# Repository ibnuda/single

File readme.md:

# Single PCB

## What?

Per switch pcb for handwiring build.

## Why?

Just because.

## Measurement

17mm x 14mm.

## Intended Use

Use it to build keyboard that is generated from [this generator](http://dactyl.siskam.link).

## Licence

GPLv3.

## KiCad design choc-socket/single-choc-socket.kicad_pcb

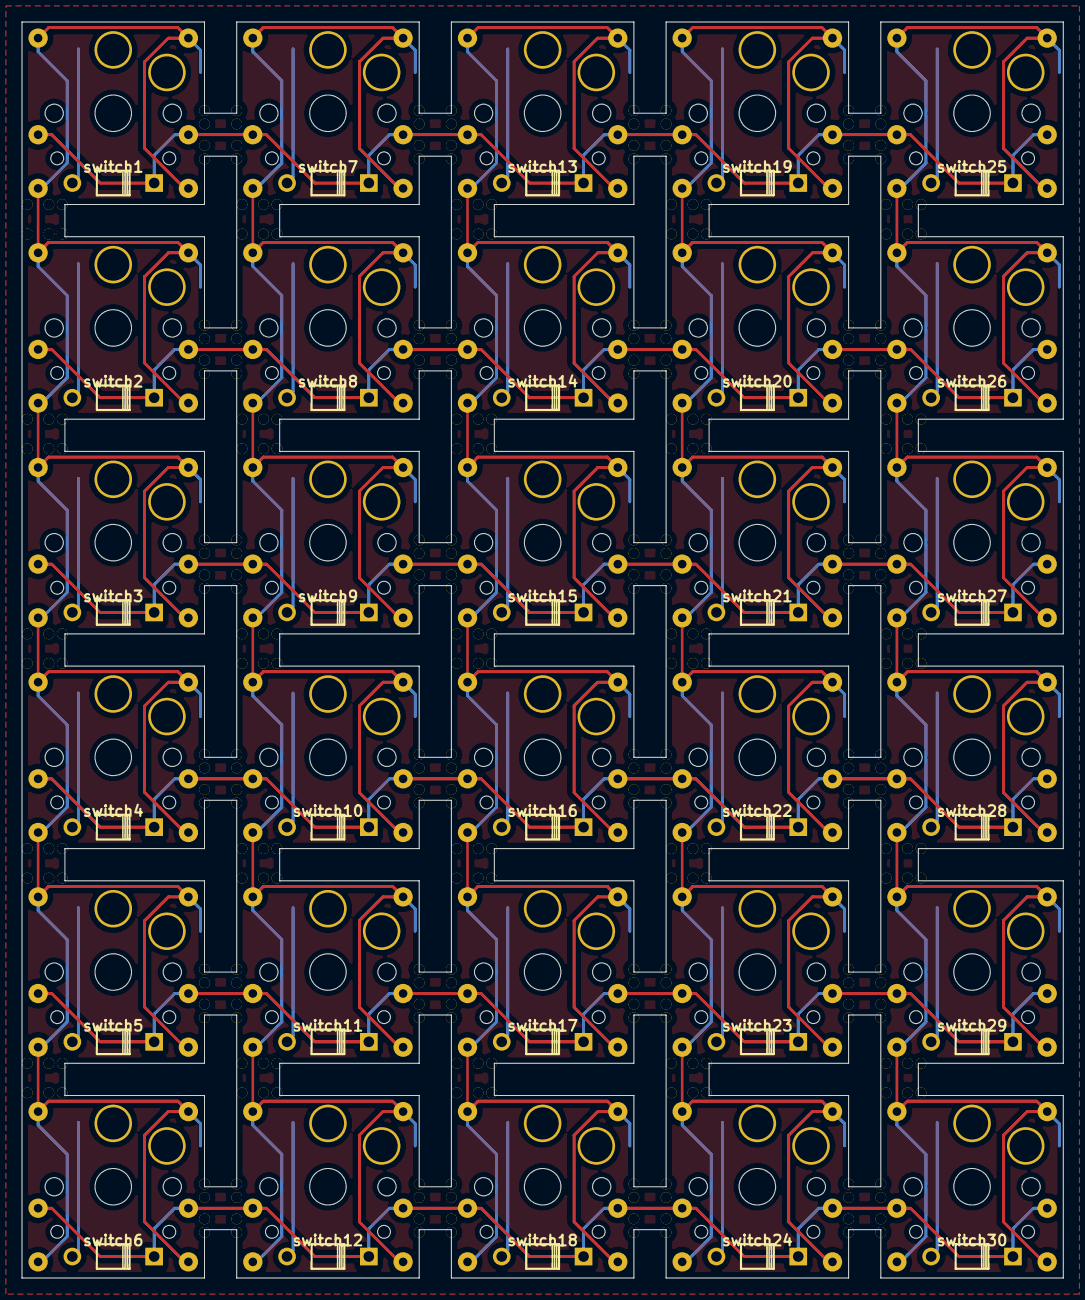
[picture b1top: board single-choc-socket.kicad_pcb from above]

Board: 2 copper layers, 97.0 x 117.0 mm, 339 parts (0 on the bottom side), 41 nets.

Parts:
J1, J2, J3, J4, J5, J6, J7, J8, J9, J10, J11, J12, J13, J14, J15, J16, J17, J18, J19, J20, J21, J22, J23, J24, J25, J26, J27, J28, J29, J30, J31, J32, J33, J34, J35, J36, J37, J38, J39, J40, J41, J42, J43, J44, J45, J46, J47, J48, J49, J50, J51, J52, J53, J54, J55, J56, J57, J58, J59, J60, J61, J62, J63, J64, J65, J66, J67, J68, J69, J70, J71, J72, J73, J74, J75, J76, J77, J78, J79, J80, J81, J82, J83, J84, J85, J86, J87, J88, J89, J90, J91, J92, J93, J94, J95, J96, J97, J98, J99, J100, J101, J102, J103, J104, J105, J106, J107, J108, J109, J110, J111, J112, J113, J114, J115, J116, J117, J118, J119, J120, J121, J122, J123, J124, J125, J126, J127, J128, J129, J130, J131, J132, J133, J134, J135, J136, J137, J138, J139, J140, J141, J142, J143, J144, J145, J146, J147, J148, J149, J150, J151, J152, J153, J154, J155, J156, J157, J158, J159, J160, J161, J162, J163, J164, J165, J166, J167, J168, J169, J170, J171, J172, J173, J174, J175, J176, J177, J178, J179, J180: Conn_01x01; wirepad
Ref**: Val**; hole-four
Ref**#2, Ref**#5, Ref**#9, Ref**#11, Ref**#14, Ref**#17, Ref**#20, Ref**#22, Ref**#26, Ref**#27, Ref**#30, Ref**#32, Ref**#34, Ref**#35, Ref**#36, Ref**#39, Ref**#40, Ref**#42, Ref**#44, Ref**#45, Ref**#47, Ref**#49, Ref**#51, Ref**#53, Ref**#55, Ref**#57, Ref**#59, Ref**#61, Ref**#64, Ref**#65, Ref**#68, Ref**#69, Ref**#70, Ref**#73, Ref**#75, Ref**#76, Ref**#78, Ref**#80, Ref**#81, Ref**#83, Ref**#85, Ref**#87, Ref**#88, Ref**#90, Ref**#91, Ref**#94, Ref**#95: Val**; hole-four
Ref**#3, Ref**#4, Ref**#6, Ref**#7, Ref**#8, Ref**#10, Ref**#12, Ref**#13, Ref**#15, Ref**#16, Ref**#18, Ref**#19, Ref**#21, Ref**#23, Ref**#24, Ref**#25, Ref**#28, Ref**#29, Ref**#31, Ref**#33, Ref**#37, Ref**#38, Ref**#41, Ref**#43, Ref**#46, Ref**#48, Ref**#50, Ref**#52, Ref**#54, Ref**#56, Ref**#58, Ref**#60, Ref**#62, Ref**#63, Ref**#66, Ref**#67, Ref**#71, Ref**#72, Ref**#74, Ref**#77, Ref**#79, Ref**#82, Ref**#84, Ref**#86, Ref**#89, Ref**#92, Ref**#93, Ref**#96, Ref**#97, Ref**#98, Ref**#99: Val**; hole-three
diode1, diode2, diode3, diode4, diode5, diode6, diode7, diode8, diode9, diode10, diode11, diode12, diode13, diode14, diode15, diode16, diode17, diode18, diode19, diode20, diode21, diode22, diode23, diode24, diode25, diode26, diode27, diode28, diode29, diode30: diode
switch1, switch2, switch3, switch4, switch5, switch6, switch7, switch8, switch9, switch10, switch11, switch12, switch13, switch14, switch15, switch16, switch17, switch18, switch19, switch20, switch21, switch22, switch23, switch24, switch25, switch26, switch27, switch28, switch29, switch30: switch; choc-1-socket

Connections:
unnamed: J1.1, J2.1, J3.1, J4.1, J5.1, J6.1, J7.1, J8.1, J9.1, J10.1, J11.1, J12.1, J13.1, J14.1, J15.1, J16.1, J17.1, J18.1, J19.1, J20.1, J21.1, J22.1, J23.1, J24.1, switch1.2, switch2.2, switch3.2, switch4.2, switch5.2, switch6.2
unnamed: J25.1, J26.1, J27.1, J28.1, J29.1, J30.1, J31.1, J32.1, J33.1, J34.1, J35.1, J36.1, J37.1, J38.1, J39.1, J40.1, J41.1, J42.1, J43.1, J44.1, J45.1, J46.1, J47.1, J48.1, switch7.2, switch8.2, switch9.2, switch10.2, switch11.2, switch12.2
unnamed: J49.1, J50.1, J51.1, J52.1, J53.1, J54.1, J55.1, J56.1, J57.1, J58.1, J59.1, J60.1, J61.1, J62.1, J63.1, J64.1, J65.1, J66.1, J67.1, J68.1, J69.1, J70.1, J71.1, J72.1, switch13.2, switch14.2, switch15.2, switch16.2, switch17.2, switch18.2
unnamed: J73.1, J74.1, J75.1, J76.1, J77.1, J78.1, J79.1, J80.1, J81.1, J82.1, J83.1, J84.1, J85.1, J86.1, J87.1, J88.1, J89.1, J90.1, J91.1, J92.1, J93.1, J94.1, J95.1, J96.1, switch19.2, switch20.2, switch21.2, switch22.2, switch23.2, switch24.2
unnamed: J97.1, J98.1, J99.1, J100.1, J101.1, J102.1, J103.1, J104.1, J105.1, J106.1, J107.1, J108.1, J109.1, J110.1, J111.1, J112.1, J113.1, J114.1, J115.1, J116.1, J117.1, J118.1, J119.1, J120.1, switch25.2, switch26.2, switch27.2, switch28.2, switch29.2, switch30.2
unnamed: J121.1, J122.1, J131.1, J132.1, J141.1, J142.1, J151.1, J152.1, J161.1, J162.1, diode1.1, diode7.1, diode13.1, diode19.1, diode25.1
unnamed: J123.1, J124.1, J133.1, J134.1, J143.1, J144.1, J153.1, J154.1, J163.1, J164.1, diode2.1, diode8.1, diode14.1, diode20.1, diode26.1
unnamed: J125.1, J126.1, J135.1, J136.1, J145.1, J146.1, J155.1, J156.1, J165.1, J166.1, diode3.1, diode9.1, diode15.1, diode21.1, diode27.1
unnamed: J127.1, J128.1, J137.1, J138.1, J147.1, J148.1, J157.1, J158.1, J167.1, J168.1, diode4.1, diode10.1, diode16.1, diode22.1, diode28.1
unnamed: J129.1, J130.1, J139.1, J140.1, J149.1, J150.1, J159.1, J160.1, J169.1, J170.1, diode5.1, diode11.1, diode17.1, diode23.1, diode29.1
unnamed: J171.1, J172.1, J173.1, J174.1, J175.1, J176.1, J177.1, J178.1, J179.1, J180.1, diode6.1, diode12.1, diode18.1, diode24.1, diode30.1
unnamed: diode1.2, switch1.1
unnamed: diode2.2, switch2.1
unnamed: diode3.2, switch3.1
unnamed: diode4.2, switch4.1
unnamed: diode5.2, switch5.1
unnamed: diode6.2, switch6.1
unnamed: diode7.2, switch7.1
unnamed: diode8.2, switch8.1
unnamed: diode9.2, switch9.1
unnamed: diode10.2, switch10.1
unnamed: diode11.2, switch11.1
unnamed: diode12.2, switch12.1
unnamed: diode13.2, switch13.1
unnamed: diode14.2, switch14.1
unnamed: diode15.2, switch15.1
unnamed: diode16.2, switch16.1
unnamed: diode17.2, switch17.1
unnamed: diode18.2, switch18.1
unnamed: diode19.2, switch19.1
unnamed: diode20.2, switch20.1
unnamed: diode21.2, switch21.1
unnamed: diode22.2, switch22.1
unnamed: diode23.2, switch23.1
unnamed: diode24.2, switch24.1
unnamed: diode25.2, switch25.1
unnamed: diode26.2, switch26.1
unnamed: diode27.2, switch27.1
unnamed: diode28.2, switch28.1
unnamed: diode29.2, switch29.1
unnamed: diode30.2, switch30.1

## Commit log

2020-05-24 init commit.
2020-05-24 6x5.
2020-05-24 Added README and License.
2020-05-25 hotswap socket.
2020-05-26 hilih kintil
2020-05-26 will jlc accept this shit? to be concluded.
2020-05-26 please let this one through, jlc.
2020-08-03 larger snappy hole thingy.
2020-08-06 new variant. unfinished.
2020-08-22 choc
    chockondiks
    -- bakingpy.
2020-08-22 finished
2020-10-06 wat?
2020-12-05 i forgot what i did.
2021-08-09 accepted by jlc per this commit.
2021-11-19 removed libs to make place for submodule
2021-11-19 updated the reference to the libs.
2021-11-19 choc socket.
2021-11-19 zone.
